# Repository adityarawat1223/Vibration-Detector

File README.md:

# Vibration Diagnostic Tool

A vibration diagnostic tool capable of detecting faulty bearings using a real-time frequency graph displayed on an OLED screen.

## Hardware ([Schematic](./Hardware/Docs/VibrationDT(Schematic).pdf))

Components Bill of Materials: [BOM](./Hardware/Assembly/)

.png)

.png)

### Working

#### 1. USB-C 6P (Power Only)
There are 6 pins on this USB-C receptacle. I am explaining 3 of them; the other 3 are symmetrical so the cable works when flipped:

* **A5 (B5):** The CC1 pin (CC2 if flipped). This pin tells the power source whether to supply power. The host leaves $V_{BUS}$ unpowered by default. When plugged in, our board pulls this line down to ground using a $5.1\text{ k}\Omega$ resistor. This creates a predictable voltage drop that signals the USB source to supply $5\text{V}$ over $V_{BUS}$.
* **A9 (B9):** $V_{BUS}$ ($5\text{V}$ power rail).
* **A12 (B12):** Ground return path.

#### 2. 3.3V LDO
To avoid frying the STM32F103C8T6 pins, we use an LDO regulator to step down the $5\text{V}$ rail to a stable, clean $3.3\text{V}$.

#### 3. STM32F103C8T6
Why this chip? It is one of the most cost-effective microcontrollers that gets the job done. It fits both the computational requirements for on-device processing and the budget constraints of the board.

#### 4. MPU-6050
A sensor containing an accelerometer and gyroscope. Since we communicate over the $I^2C$ protocol, sampling is typically limited to $100\text{--}400\text{ Hz}$ (the primary communication bottleneck).

#### 5. Miscellaneous
* **5-pin Header:** For programming and debugging the MCU (SWD interface).
* **4-pin Header:** For connecting the OLED display to the MCU via $I^2C$.
* **SW1 Switch:** Pulls the `BOOT0` pin high to enter the internal bootloader.
* **SW2 Switch:** Pulls the `NRST` pin low to reset the MCU.
* **Capacitors & Resistors:** High-frequency decoupling capacitors placed close to the MCU power pins, bulk filtering caps, and necessary pull-up/pull-down resistors.

## Firmware

We have coded the firmware in bare C for learning purposes. You can find all the information in the datasheets or reference manuals, which I have listed here:

* [STM32F103C8 Datasheet](https://www.st.com/resource/en/datasheet/stm32f103c8.pdf)
* [STM32F103 Reference Manual](https://www.st.com/resource/en/reference_manual/rm0008-stm32f101xx-stm32f102xx-stm32f103xx-stm32f105xx-and-stm32f107xx-advanced-armbased-32bit-mcus-stmicroelectronics.pdf)
* [MPU-6050 Specifications](https://cdn.sparkfun.com/datasheets/Components/General%20IC/PS-MPU-6000A.pdf)

### Explanation 

Initially, clocks are disabled for peripherals. If you look at the memory map in the datasheets of the STM32, you will see that we enabled the clock for I2C2 using:
```c
RCC_APB1ENR |= (1 << 22);
```
And enabled the clock for Port B and AFIO (Alternate Function I/O) using:
```c
RCC_APB2ENR |= (1 << 0);
RCC_APB2ENR |= (1 << 3);
```

If you take a look at the other init functions, similar things are done where we are just enabling the functionalities we want by following the datasheet instructions.

#### Reading MPU-6050
For reading data from the MPU, we are using the $I^2C$ protocol. That is why we have two pins, PB10 and PB11, working as SCL and SDA respectively.

First, we generate the START condition by setting the 8th bit HIGH in `I2C2_CR1` (Control Register 1), then wait for the start bit to be set using Status Register 1 (`I2C2_SR1`).

Then, by reading the registers like this:
```c
temp = I2C2_SR1;
temp = I2C2_SR2;
(void)temp;
```
You are essentially clearing the `ADDR` flag. Then we send `0x3B` using the data register, which is the internal register address of the accelerometer on the MPU to start reading from.

Before we move forward, I would like to highlight that we are getting 6 bytes of data from the MPU, which represents 16-bit acceleration data for the X, Y, and Z axes.

We continue reading data according to the datasheet. Once we read the 4th byte (index 3 in code), the 5th byte is already in the data register. Because the STM32 operates using one internal shift register and one data register, our 6th byte (which is the last byte) is already in the shift register. So, we can safely pull ACK down to LOW (send NACK) and generate the STOP condition before reading the final values.

#### Algorithm 

We used the Cooley–Tukey Radix-2 FFT algorithm. Since the mathematical derivation is quite lengthy .
Heres a good article about it :-
[FFT](https://brianmcfee.net/dstbook-site/content/ch08-fft/FFT.html)

---

## Disclaimer

This is a student hobby and learning project built for experimenting with bare-metal programming and vibration analysis. It is not intended for safety-critical or certified industrial machinery monitoring.

## License

This project is open-source under the [MIT License](LICENSE). Feel free to use the code and hardware design for your own learning or projects!

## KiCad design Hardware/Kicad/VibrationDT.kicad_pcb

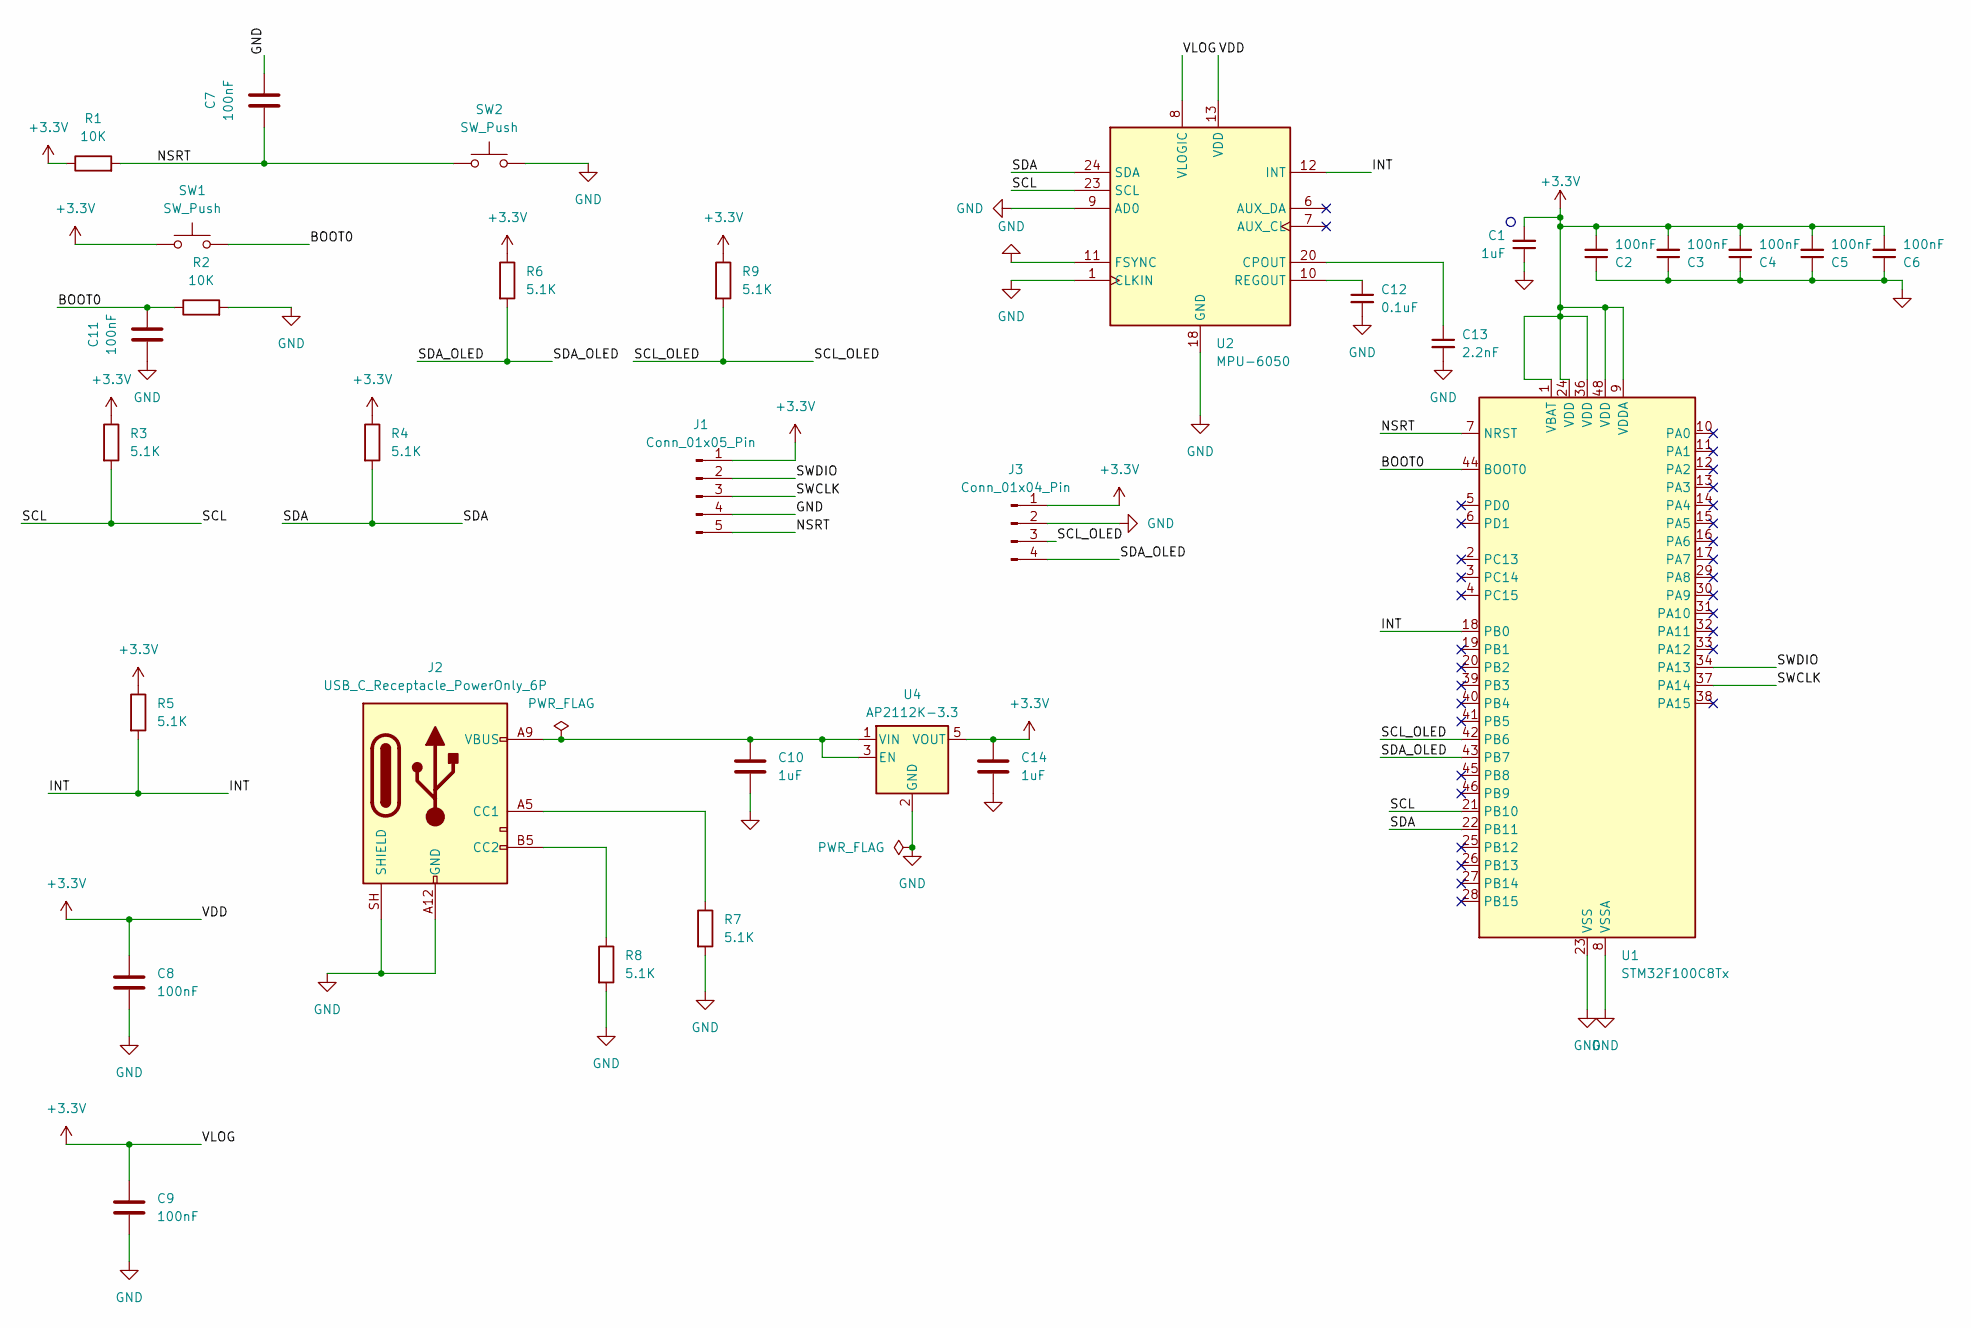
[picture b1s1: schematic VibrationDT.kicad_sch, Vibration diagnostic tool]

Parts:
C1, C10, C14: 1uF; C_0805_2012Metric
C2, C3, C4, C5, C6, C7, C8, C9, C11: 100nF; C_0805_2012Metric
C12: 0.1uF; C_0805_2012Metric
C13: 2.2nF; C_0805_2012Metric
J1: Conn_01x05_Pin; PinHeader_1x05_P2.54mm_Vertical_SMD_Pin1Left
J2: USB_C_Receptacle_PowerOnly_6P; USB_C_Receptacle_GCT_USB4125-xx-x_6P_TopMnt_Horizontal
J3: Conn_01x04_Pin; PinHeader_1x04_P2.00mm_Vertical_SMD_Pin1Left
R1, R2: 10K; R_0805_2012Metric
R3, R4, R5, R6, R7, R8, R9: 5.1K; R_0805_2012Metric
SW1, SW2: SW_Push; SW_SPST_PTS645Sx43SMTR92
U1: STM32F100C8Tx; LQFP-48_7x7mm_P0.5mm
U2: MPU-6050; InvenSense_QFN-24_4x4mm_P0.5mm
U4: AP2112K-3.3; SOT-23-5

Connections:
+3.3V: C1.2, C2.2, C3.2, C4.2, C5.2, C6.2, C8.1, C9.1, C14.1, J1.1, J3.1, R1.1, R3.1, R4.1, R5.1, R6.1, R9.1, SW1.1, U1.1 (VBAT), U1.9 (VDDA), U1.24 (VDD), U1.36 (VDD), U1.48 (VDD), U2.8 (VLOGIC), U2.13 (VDD), U4.5 (VOUT)
/BOOT0: C11.2, R2.1, SW1.2, U1.44 (BOOT0)
/INT: R5.2, U1.18 (PB0), U2.12 (INT)
/NSRT: C7.1, J1.5, R1.2, SW2.1, U1.7 (NRST)
/SCL: R3.2, U1.21 (PB10), U2.23 (SCL)
/SCL_OLED: J3.3, R9.2, U1.42 (PB6)
/SDA: R4.2, U1.22 (PB11), U2.24 (SDA)
/SDA_OLED: J3.4, R6.2, U1.43 (PB7)
/SWCLK: J1.3, U1.37 (PA14)
/SWDIO: J1.2, U1.34 (PA13)
GND: C1.1, C2.1, C3.1, C4.1, C5.1, C6.1, C7.2, C8.2, C9.2, C10.2, C11.1, C12.2, C13.2, C14.2, J1.4, J2.A12 (GND), J2.B12 (GND), J2.SH (SHIELD), J3.2, R2.2, R7.2, R8.2, SW2.2, U1.8 (VSSA), U1.23 (VSS), U1.35 (VSS), U1.47 (VSS), U2.1 (CLKIN), U2.9 (AD0), U2.11 (FSYNC), U2.18 (GND), U4.2 (GND)
unnamed: J2.A5 (CC1), R7.1
unnamed: J2.B5 (CC2), R8.1
unnamed: C13.1, U2.20 (CPOUT)
unnamed: C12.1, U2.10 (REGOUT)
unnamed: C10.1, J2.A9 (VBUS), J2.B9 (VBUS), U4.1 (VIN), U4.3 (EN)

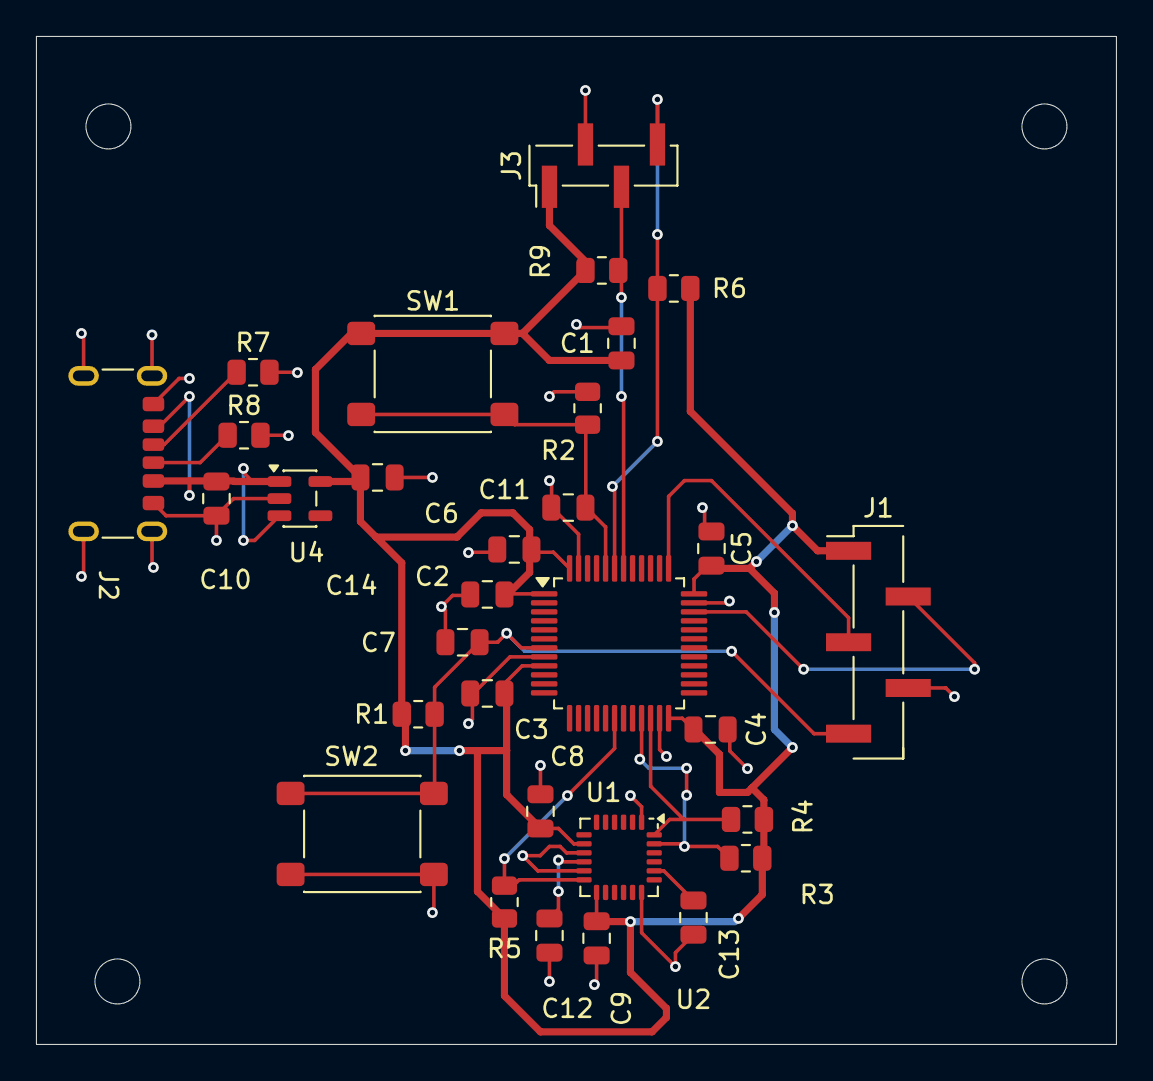
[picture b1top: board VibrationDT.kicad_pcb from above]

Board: 2 copper layers, 60.0 x 56.0 mm, 31 parts (0 on the bottom side), 16 nets.
